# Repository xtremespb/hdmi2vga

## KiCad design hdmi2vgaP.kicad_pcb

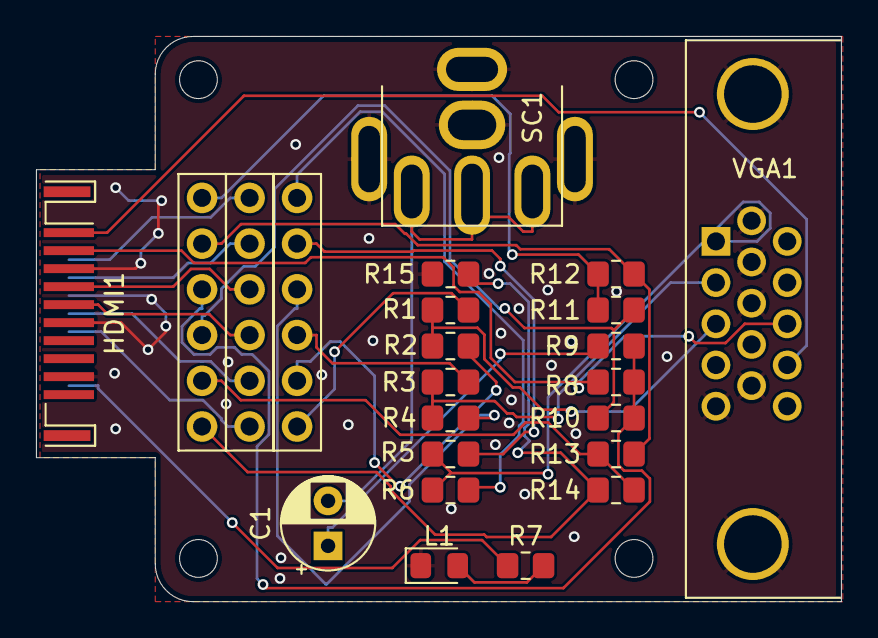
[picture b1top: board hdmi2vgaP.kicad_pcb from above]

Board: 2 copper layers, 44.7 x 31.4 mm, 27 parts (0 on the bottom side), 28 nets.

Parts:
C1: 220u; Medved_CP_Radial_D5.0mm_P2.50mm
H1, H2, H3, H4: MountingHole; MountingHole_2.1mm
HDMI1: HDMI; HDMI_A_Contact_Technology_HDMI-19APL2_Horizontal
J1: HDMI; Medved_Pinheader_6P
J2: VGA; Medved_Pinheader_6P
J3: Composite; Medved_Pinheader_6P
L1: HDMI LED; LED_0805_2012Metric_Pad1.15x1.40mm_HandSolder
R1, R3, R5: 820R; R_0805_2012Metric_Pad1.20x1.40mm_HandSolder
R2, R4, R6: 0R; R_0805_2012Metric_Pad1.20x1.40mm_HandSolder
R7: 1K; R_0805_2012Metric_Pad1.20x1.40mm_HandSolder
R8: 510R*; R_0805_2012Metric_Pad1.20x1.40mm_HandSolder
R9: 51R*; R_0805_2012Metric_Pad1.20x1.40mm_HandSolder
R10, R11, R12, R13, R14: 150R; R_0805_2012Metric_Pad1.20x1.40mm_HandSolder
R15: 300R; R_0805_2012Metric_Pad1.20x1.40mm_HandSolder
SC1: VIDEO (Soft Composite); AV_MOD_III-8.4-5
VGA1: VGA; Medved_DSUB-15-HD_Female_Horizontal

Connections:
/HDMI/CLKN: HDMI1.12 (CLKN), J1.1
/HDMI/CLKP: HDMI1.10 (CLKP), J1.2
/HDMI/D0N: HDMI1.9 (D0N), J1.3
/HDMI/D0P: HDMI1.7 (D0P), J1.4
/HDMI/D1N: HDMI1.6 (D1N), J1.5
/HDMI/D1P: HDMI1.4 (D1P), J1.6
/HDMI/D2N: HDMI1.3 (D2N), R8.1, VGA1.13
/HDMI/D2P: HDMI1.1 (D2P), VGA1.14
/HDMI/VBUS: HDMI1.18 (+5V), R7.1
/Soft Composite/CLKN: J3.1, R14.1, R15.2
/Soft Composite/CLKP: J3.2, R13.1, R14.2
/Soft Composite/CVBS: C1.2, SC1.1
/Soft Composite/D0N: J3.3, R10.1, R11.2
/Soft Composite/D0P: J3.4, R8.2, R9.1, R10.2
/Soft Composite/D1N: J3.5, R12.1, R13.2
/Soft Composite/D1P: J3.6, R11.1, R12.2
/VGA/VGA_BH: R1.2, R2.2, VGA1.3
/VGA/VGA_GH: R3.2, R4.2, VGA1.2
/VGA/VGA_RH: R5.2, R6.2, VGA1.1
GND: HDMI1.2 (G_D2), HDMI1.5 (G_D1), HDMI1.8 (G_D0), HDMI1.11 (G_CLK), HDMI1.17 (G_DDC/CEC), L1.1 (K), R15.1, SC1.2, VGA1.0, VGA1.5, VGA1.6, VGA1.7, VGA1.8, VGA1.10
unnamed: C1.1, R9.2
unnamed: J2.1, R1.1
unnamed: J2.2, R2.1
unnamed: J2.3, R3.1
unnamed: J2.4, R4.1
unnamed: J2.5, R5.1
unnamed: J2.6, R6.1
unnamed: L1.2 (A), R7.2

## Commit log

2024-12-03 HW Rev 1.0
2024-12-03 Updates to HW Rev 1.0
2024-12-03 Schematics added
2024-12-29 HW Rev 2.0
2024-12-29 3D Case for HW Rev 1.0
2025-01-14 Minor updates
2025-01-14 Minor updates to HW REV 2.0
2025-01-29 Case added
